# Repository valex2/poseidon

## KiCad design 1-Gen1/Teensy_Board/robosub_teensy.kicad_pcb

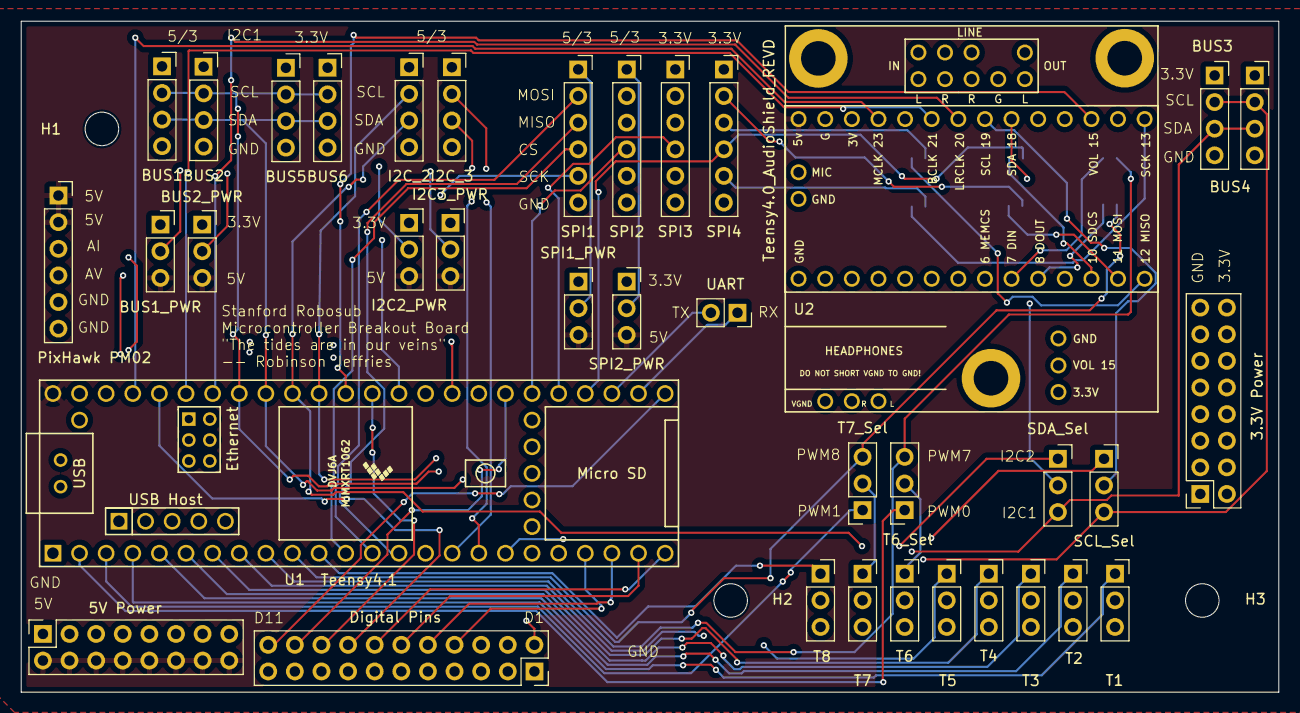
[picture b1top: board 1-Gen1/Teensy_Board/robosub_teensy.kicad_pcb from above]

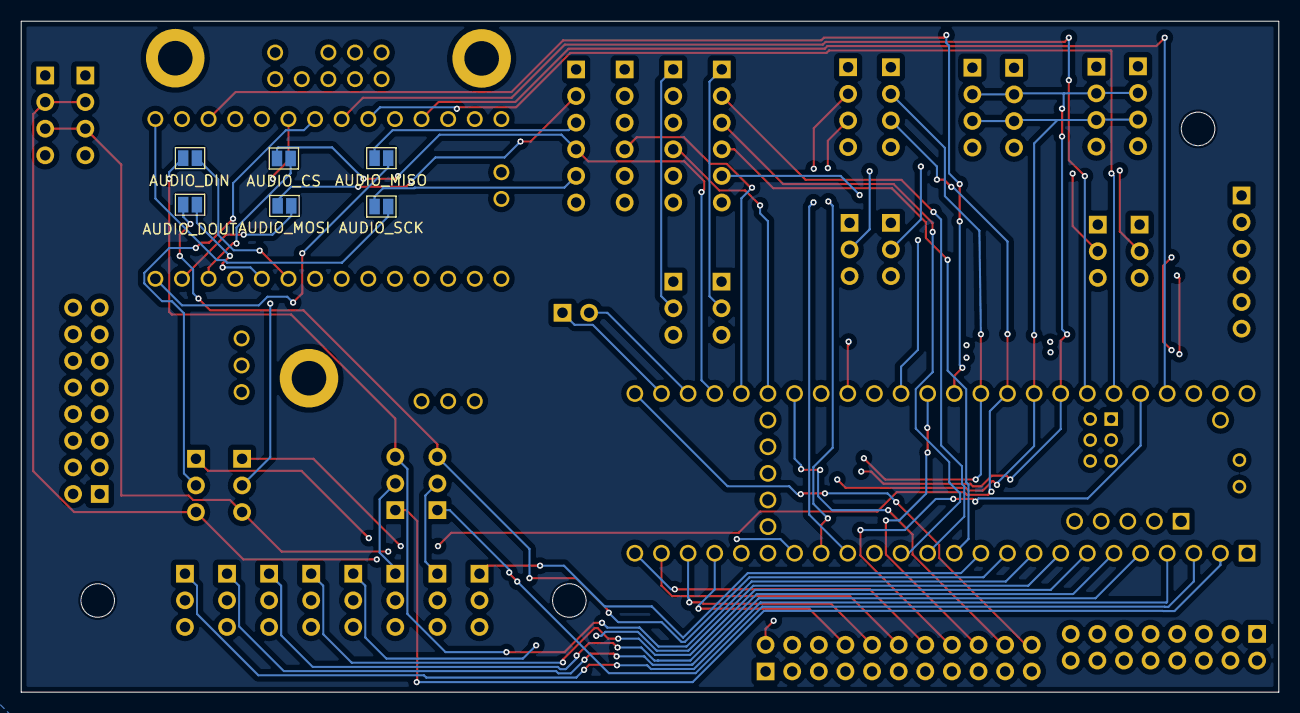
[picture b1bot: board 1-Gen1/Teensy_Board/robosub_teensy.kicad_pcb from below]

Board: 4 copper layers, 120.0 x 64.0 mm, 46 parts (6 on the bottom side), 61 nets.

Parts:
H1, H2, H3: MountingHole; MountingHole_3.2mm_M3
J1: T1; PinSocket_1x03_P2.54mm_Vertical
J2: UART; PinSocket_1x02_P2.54mm_Vertical
J3: T2; PinSocket_1x03_P2.54mm_Vertical
J4: T6; PinSocket_1x03_P2.54mm_Vertical
J5: T3; PinSocket_1x03_P2.54mm_Vertical
J6: T7; PinSocket_1x03_P2.54mm_Vertical
J7: T4; PinSocket_1x03_P2.54mm_Vertical
J8: T8; PinSocket_1x03_P2.54mm_Vertical
J9: T5; PinSocket_1x03_P2.54mm_Vertical
J10: PixHawk PM02; PinSocket_1x06_P2.54mm_Vertical
J11: 3.3V Power; PinSocket_2x08_P2.54mm_Vertical
J12: 5V Power; PinSocket_2x08_P2.54mm_Vertical
J13: BUS1; PinSocket_1x04_P2.54mm_Vertical
J14: BUS2; PinSocket_1x04_P2.54mm_Vertical
J17: Digital Pins; PinSocket_2x11_P2.54mm_Vertical
J18: BUS3; PinSocket_1x04_P2.54mm_Vertical
J19: BUS4; PinSocket_1x04_P2.54mm_Vertical
J20: BUS5; PinSocket_1x04_P2.54mm_Vertical
J21: BUS6; PinSocket_1x04_P2.54mm_Vertical
J22: SPI1; PinSocket_1x06_P2.54mm_Vertical
J23: SPI2; PinSocket_1x06_P2.54mm_Vertical
J24: I2C_2; PinSocket_1x04_P2.54mm_Vertical
J25: I2C_3; PinSocket_1x04_P2.54mm_Vertical
J26: SPI3; PinSocket_1x06_P2.54mm_Vertical
J27: SPI4; PinSocket_1x06_P2.54mm_Vertical
JP1: BUS1_PWR; PinSocket_1x03_P2.54mm_Vertical
JP2: BUS2_PWR; PinSocket_1x03_P2.54mm_Vertical
JP3: T6_Sel; PinSocket_1x03_P2.54mm_Vertical
JP4: T7_Sel; PinSocket_1x03_P2.54mm_Vertical
JP7: SPI1_PWR; PinSocket_1x03_P2.54mm_Vertical
JP8: SPI2_PWR; PinSocket_1x03_P2.54mm_Vertical
JP9: I2C2_PWR; PinSocket_1x03_P2.54mm_Vertical
JP10: I2C3_PWR; PinSocket_1x03_P2.54mm_Vertical
JP11: AUDIO_DIN; SolderJumper-2_P1.3mm_Open_Pad1.0x1.5mm
JP12: AUDIO_DOUT; SolderJumper-2_P1.3mm_Open_Pad1.0x1.5mm
JP13: AUDIO_CS; SolderJumper-2_P1.3mm_Open_Pad1.0x1.5mm
JP14: AUDIO_MOSI; SolderJumper-2_P1.3mm_Open_Pad1.0x1.5mm
JP15: AUDIO_MISO; SolderJumper-2_P1.3mm_Open_Pad1.0x1.5mm
JP16: AUDIO_SCK; SolderJumper-2_P1.3mm_Open_Pad1.0x1.5mm
JP17: SDA_Sel; PinSocket_1x03_P2.54mm_Vertical
JP18: SCL_Sel; PinSocket_1x03_P2.54mm_Vertical
U1: Teensy4.1; Teensy41
U2: Teensy4.0_AudioShield_REVD; 4.0audioshield

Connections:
+3.3V: J11.2, J11.4, J11.6, J11.8, J11.10, J11.12, J11.14, J11.16, J18.1, J19.1, J20.1, J21.1, J26.1, J27.1, JP1.1 (A), JP2.1 (A), JP7.1 (A), JP8.1 (A), JP9.1 (A), JP10.1 (A), U1.15 (3V3), U1.46 (3V3), U2.28 (3V)
+5V: J10.1, J10.2, J12.2, J12.4, J12.6, J12.8, J12.10, J12.12, J12.14, J12.16, JP1.3 (B), JP2.3 (B), JP7.3 (B), JP8.3 (B), JP9.3 (B), JP10.3 (B), U1.48 (VIN), U2.30 (5V)
Analog_Current: J10.3, U1.33 (41_A17)
Analog_Voltage: J10.4, U1.32 (40_A16)
BCLK: U1.43 (21_A7_RX5_BCLK1), U2.25 (21_A7_RX5_BCLK1)
D1/A1: J17.2, U1.18 (26_A12_MOSI1)
D2/A2: J17.4, U1.19 (27_A13_SCK1)
D3/PWM10: J17.6, U1.20 (28_RX7)
D4/PWM11: J17.8, U1.21 (29_TX7)
D5: J17.10, U1.22 (30_CRX3)
D6: J17.12, U1.23 (31_CTX3)
D7: J17.14, U1.24 (32_OUT1B)
D8/A3/PWM12: J17.16, U1.44 (22_A8_CTX1)
D9/A4/PWM13: J17.18, U1.36 (14_A0_TX3_SPDIF_OUT)
D10/A5: J17.20, U1.31 (39_MISO1_OUT1A)
D11/PWM14: J17.22, U1.25 (33_MCLK2)
GND: J1.3, J3.3, J4.3, J5.3, J6.3, J7.3, J8.3, J9.3, J10.5, J10.6, J11.1, J11.3, J11.5, J11.7, J11.9, J11.11, J11.13, J11.15, J12.1, J12.3, J12.5, J12.7, J12.9, J12.11, J12.13, J12.15, J13.4, J14.4, J17.1, J17.3, J17.5, J17.7, J17.9, J17.11, J17.13, J17.15, J17.17, J17.19, J17.21, J18.4, J19.4, J20.4, J21.4, J22.6, J23.6, J24.4, J25.4, J26.6, J27.6, U1.1 (GND), U1.34 (GND), U1.47 (GND), U2.1 (GND), U2.29 (GND)
I2C1_SCL: J13.2, J14.2, J18.2, J19.2, J20.2, J21.2, JP18.3 (B), U1.41 (19_A5_SCL)
I2C1_SDA: J13.3, J14.3, J18.3, J19.3, J20.3, J21.3, JP17.3 (B), U1.40 (18_A4_SDA)
I2C2_SCL: J24.2, JP18.1 (A), U1.38 (16_A2_RX4_SCL1)
I2C2_SDA: J24.3, JP17.1 (A), U1.39 (17_A3_TX4_SDA1)
I2C3_SCL: J25.2, U1.16 (24_A10_TX6_SCL2)
I2C3_SDA: J25.3, U1.17 (25_A11_RX6_SDA2)
LRCLK: U1.42 (20_A6_TX5_LRCLK1), U2.24 (20_A6_TX5_LRCLK1)
MCLK: U1.45 (23_A9_CRX1_MCLK1), U2.27 (23_A9_CRX1_MCLK1)
unnamed: J4.1, JP3.2 (C)
unnamed: J6.1, JP4.2 (C)
unnamed: J13.1, JP1.2 (C)
unnamed: J14.1, JP2.2 (C)
unnamed: J22.1, JP7.2 (C)
unnamed: J23.1, JP8.2 (C)
unnamed: J24.1, JP9.2 (C)
unnamed: J25.1, JP10.2 (C)
unnamed: JP11.2 (B), U2.9 (7_RX2_OUT1A)
unnamed: JP12.2 (B), U2.10 (8_TX2_IN1)
unnamed: JP13.2 (B), U2.12 (10_CS_MQSR)
unnamed: JP14.2 (B), U2.13 (11_MOSI_CTX1)
unnamed: JP15.2 (B), U2.14 (12_MISO_MQSL)
unnamed: JP16.2 (B), U2.17 (13_SCK_CRX1_LED)
unnamed: JP17.2 (C), U2.22 (18_A4_SDA0)
unnamed: JP18.2 (C), U2.23 (19_A5_SCL0)
PWM0: JP3.1 (A), U1.2 (0_RX1_CRX2_CS1)
PWM1: JP4.1 (A), U1.3 (1_TX1_CTX2_MISO1)
PWM2: J1.1, U1.4 (2_OUT2)
PWM3: J3.1, U1.5 (3_LRCLK2)
PWM4: J5.1, U1.6 (4_BCLK2)
PWM5: J7.1, U1.7 (5_IN2)
PWM6: J9.1, U1.8 (6_OUT1D)
PWM7/AUDIO_DIN: JP3.3 (B), JP11.1 (A), U1.9 (7_RX2_OUT1A)
PWM8/AUDIO_DOUT: JP4.3 (B), JP12.1 (A), U1.10 (8_TX2_IN1)
PWM9: J8.1, U1.11 (9_OUT1C)
SPI_CS1: J22.4, U1.12 (10_CS_MQSR)
SPI_CS2: J23.4, U1.30 (38_CS1_IN1)
SPI_CS3: J26.4, U1.29 (37_CS)
SPI_CS4: J27.4, JP13.1 (A), U1.28 (36_CS)
SPI_MISO: J22.3, J23.3, J26.3, J27.3, JP15.1 (A), U1.14 (12_MISO_MQSL)
SPI_MOSI: J22.2, J23.2, J26.2, J27.2, JP14.1 (A), U1.13 (11_MOSI_CTX1)
SPI_SCK: J22.5, J23.5, J26.5, J27.5, JP16.1 (A), U1.35 (13_SCK_LED)
UART_RX: J2.1, U1.26 (34_RX8)
UART_TX: J2.2, U1.27 (35_TX8)
Vol_Knob: U1.37 (15_A1_RX3_SPDIF_IN), U2.19 (15_A1_RX3_SPDIF_IN_VOL)

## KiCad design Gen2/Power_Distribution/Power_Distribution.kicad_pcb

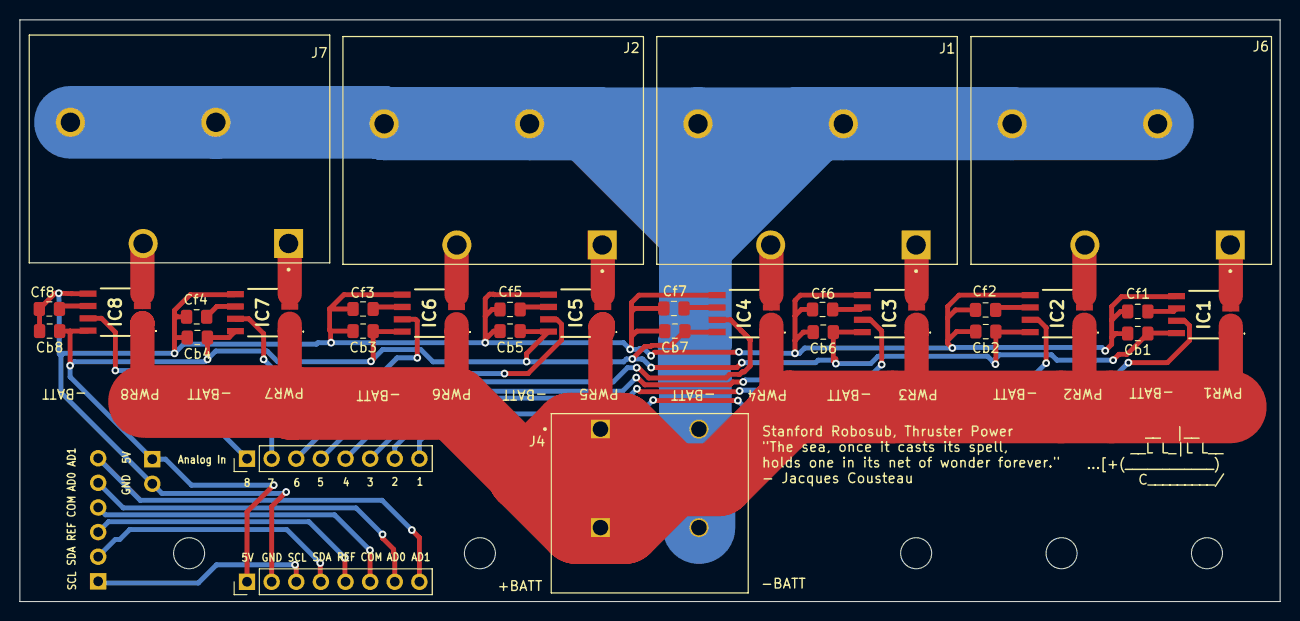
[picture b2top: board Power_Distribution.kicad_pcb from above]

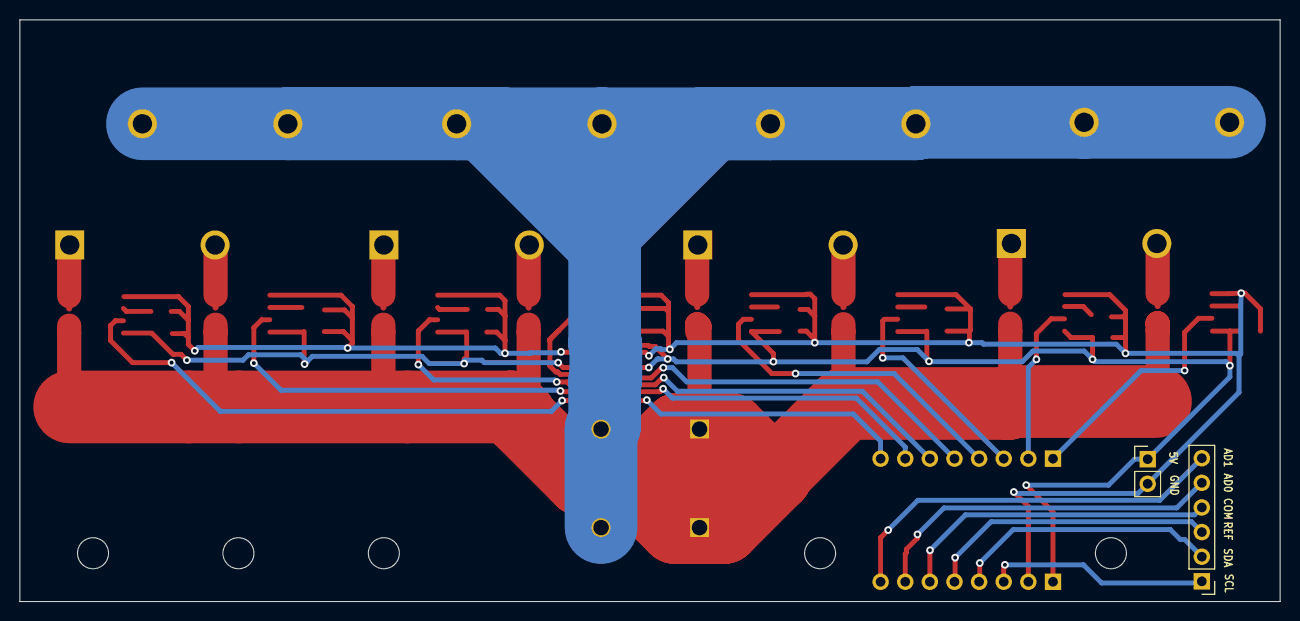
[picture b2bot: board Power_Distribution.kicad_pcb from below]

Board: 2 copper layers, 130.0 x 60.0 mm, 38 parts (2 on the bottom side), 34 nets.

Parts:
Cb1, Cb2, Cb3, Cb4, Cb5, Cb6, Cb7, Cb8: 0.1 µF; C_0805_2012Metric_Pad1.18x1.45mm_HandSolder
Cf1, Cf2, Cf3, Cf4, Cf5, Cf6, Cf7, Cf8: 100 µF; C_0805_2012Metric_Pad1.18x1.45mm_HandSolder
H1, H2, H2#2, H3, H4: MountingHole; MountingHole_3.2mm_M3
IC1, IC8: ACS713ELCTR-30A-T; ACS711ELCTR25ABT
IC2, IC3, IC4, IC5, IC6, IC7: ACS713ELCTR-30A-T; MyHalleffectSensor
J1, J2, J6, J7: 1098169; PHOENIX_1098169
J3, J9: Conn_01x08; PinHeader_1x08_P2.54mm_Vertical
J4: 1986660-2; TE_1986660-2
J5: Conn_01x06; PinHeader_1x06_P2.54mm_Vertical
J8: Conn_01x02; PinHeader_1x02_P2.54mm_Vertical

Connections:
5V: Cb1.1, Cb2.1, Cb3.1, Cb4.1, Cb5.1, Cb6.1, Cb7.1, Cb8.1, IC1.8 (VCC), IC2.8 (VCC), IC3.8 (VCC), IC4.8 (VCC), IC5.8 (VCC), IC6.8 (VCC), IC7.8 (VCC), IC8.8 (VCC), J3.1, J8.1
+BATT: IC1.1 (IP+_1), IC1.2 (IP+_2), IC2.1 (IP+_1), IC2.2 (IP+_2), IC3.1 (IP+_1), IC3.2 (IP+_2), IC4.1 (IP+_1), IC4.2 (IP+_2), IC5.1 (IP+_1), IC5.2 (IP+_2), IC6.1 (IP+_1), IC6.2 (IP+_2), IC7.1 (IP+_1), IC7.2 (IP+_2), IC8.1 (IP+_1), IC8.2 (IP+_2), J4.1_1 (1), J4.1_2 (1)
-BATT: J1.2, J1.4, J2.2, J2.4, J4.2_1 (2), J4.2_2 (2), J6.2, J6.4, J7.2, J7.4
AD0: J3.7, J5.5
AD1: J3.8, J5.6
COM: J3.6, J5.4
GND: Cb1.2, Cb2.2, Cb3.2, Cb4.2, Cb5.2, Cb6.2, Cb7.2, Cb8.2, Cf1.2, Cf2.2, Cf3.2, Cf4.2, Cf5.2, Cf6.2, Cf7.2, Cf8.2, IC1.5 (GND), IC2.5 (GND), IC3.5 (GND), IC4.5 (GND), IC5.5 (GND), IC6.5 (GND), IC7.5 (GND), IC8.5 (GND), J3.2, J8.2
unnamed: Cf1.1, IC1.6 (FILTER)
unnamed: Cf2.1, IC2.6 (FILTER)
unnamed: Cf6.1, IC3.6 (FILTER)
unnamed: Cf7.1, IC4.6 (FILTER)
unnamed: Cf5.1, IC5.6 (FILTER)
unnamed: Cf3.1, IC6.6 (FILTER)
unnamed: Cf4.1, IC7.6 (FILTER)
unnamed: Cf8.1, IC8.6 (FILTER)
PWR1: IC1.3 (IP-_1), IC1.4 (IP-_2), J6.1
PWR2: IC2.3 (IP-_1), IC2.4 (IP-_2), J6.3
PWR3: IC3.3 (IP-_1), IC3.4 (IP-_2), J1.1
PWR4: IC4.3 (IP-_1), IC4.4 (IP-_2), J1.3
PWR5: IC5.3 (IP-_1), IC5.4 (IP-_2), J2.1
PWR6: IC6.3 (IP-_1), IC6.4 (IP-_2), J2.3
PWR7: IC7.3 (IP-_1), IC7.4 (IP-_2), J7.1
PWR8: IC8.3 (IP-_1), IC8.4 (IP-_2), J7.3
REF: J3.5, J5.3
SCL: J3.3, J5.1
SDA: J3.4, J5.2
VIout1: IC1.7 (VIOUT), J9.8
VIout2: IC2.7 (VIOUT), J9.7
VIout3: IC3.7 (VIOUT), J9.6
VIout4: IC4.7 (VIOUT), J9.5
VIout5: IC5.7 (VIOUT), J9.4
VIout6: IC6.7 (VIOUT), J9.3
VIout7: IC7.7 (VIOUT), J9.2
VIout8: IC8.7 (VIOUT), J9.1

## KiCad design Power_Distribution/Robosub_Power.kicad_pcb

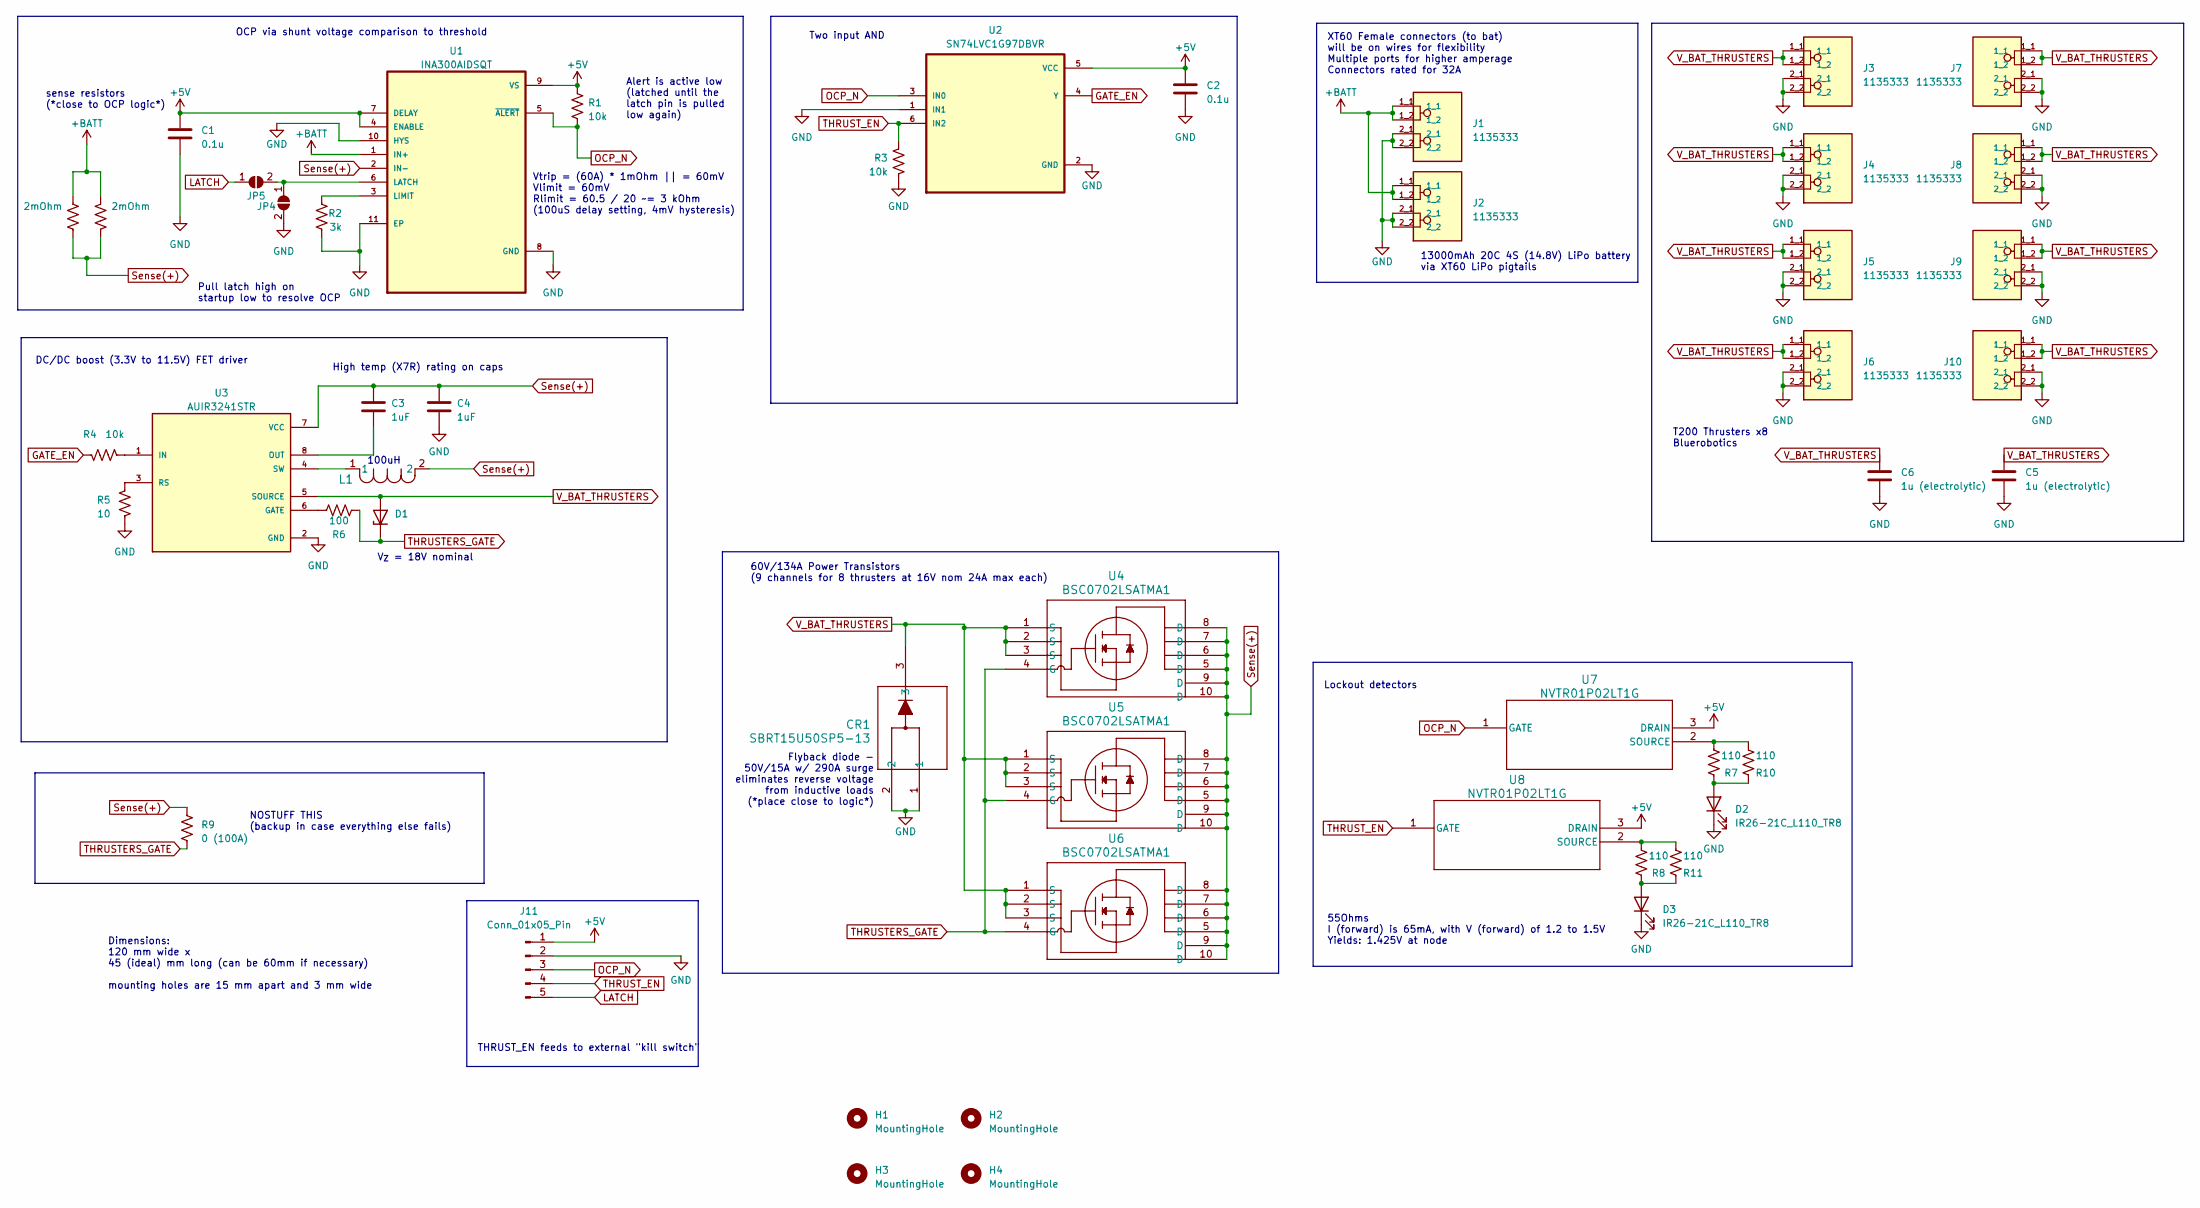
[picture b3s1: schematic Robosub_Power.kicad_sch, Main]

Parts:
C1, C2: 0.1u; C_0805_2012Metric_Pad1.18x1.45mm_HandSolder
C3, C4: 1uF; C_1812_4532Metric_Pad1.57x3.40mm_HandSolder
C5, C6: 1u (electrolytic); UCB1V0R1MCL1GS
CR1: SBRT15U50SP5-13; POWERDI5_DIO
D1: 1SMA5931BT3; D_SMA
D2, D3: IR26-21C_L110_TR8; LED_1206_3216Metric
H1, H2, H3, H4: MountingHole; MountingHole_3.2mm_M3
J1, J2, J3, J4, J5, J6, J7, J8, J9, J10: 1135333; PHOENIX_1135333
J11: Conn_01x05_Pin; PinHeader_1x05_P2.54mm_Vertical
JP4, JP5: SolderJumper_2_Open; SolderJumper-2_P1.3mm_Open_Pad1.0x1.5mm
L1: 74477420; IND_5848-WE-PD2_WRE
R1, R3, R4: 10k; R_0805_2012Metric_Pad1.20x1.40mm_HandSolder
R2: 3k; R_0805_2012Metric_Pad1.20x1.40mm_HandSolder
R5: 10; R_0805_2012Metric_Pad1.20x1.40mm_HandSolder
R6: 100; R_0805_2012Metric_Pad1.20x1.40mm_HandSolder
R7, R8, R10, R11: 110; R_0805_2012Metric_Pad1.20x1.40mm_HandSolder
R9: 0 (100A); R_2512_6332Metric_Pad1.40x3.35mm_HandSolder
U1: INA300AIDSQT; SON40P200X200X80-11N
U2: SN74LVC1G97DBVR; SOT95P280X145-6N
U3: AUIR3241STR; SOIC127P600X175-8N_AUIR3241STR
U4, U5, U6: BSC0702LSATMA1
U7, U8: NVTR01P02LT1G; SOT-23-3_1P4X3P040_ONS
WSLP59312L000FEA_1, WSLP59312L000FEA_2: 2mOhm; RES_WSLP5931_.002OHM_VIS

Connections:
+5V: C1.1, C2.1, J11.1, R1.1, U1.4 (ENABLE), U1.7 (DELAY), U1.9 (VS), U2.5 (VCC), U7.3 (DRAIN), U8.3 (DRAIN)
+BATT: J1.1_1, J1.1_2, J2.1_1, J2.1_2, U1.1 (IN+), WSLP59312L000FEA_1.2, WSLP59312L000FEA_2.2
GATE_EN: R4.1, U2.4 (Y)
GND: C1.2, C2.2, C4.2, C5.2, C6.2, CR1.1, CR1.2, D2.1 (K), D3.1 (K), J1.2_1, J1.2_2, J2.2_1, J2.2_2, J3.2_1, J3.2_2, J4.2_1, J4.2_2, J5.2_1, J5.2_2, J6.2_1, J6.2_2, J7.2_1, J7.2_2, J8.2_1, J8.2_2, J9.2_1, J9.2_2, J10.2_1, J10.2_2, J11.2, JP4.2 (B), R2.2, R3.2, R5.2, U1.8 (GND), U1.10 (HYS), U1.11 (EP), U2.1 (IN1), U2.2 (GND), U3.2 (GND)
LATCH: J11.5, JP5.1 (A)
unnamed: D2.2 (A), R7.1, R10.1
unnamed: D3.2 (A), R8.1, R11.1
unnamed: JP4.1 (A), JP5.2 (B), U1.6 (LATCH)
unnamed: R2.1, U1.3 (LIMIT)
unnamed: R6.1, U3.6 (GATE)
unnamed: R4.2, U3.1 (IN)
unnamed: C3.2, U3.8 (OUT)
unnamed: R5.1, U3.3 (RS)
unnamed: L1.1, U3.4 (SW)
unnamed: R7.2, R10.2, U7.2 (SOURCE)
unnamed: R8.2, R11.2, U8.2 (SOURCE)
OCP_N: J11.3, R1.2, U1.5 (~ALERT), U2.3 (IN0), U7.1 (GATE)
Sense(+): C3.1, C4.1, L1.2, R9.1, U1.2 (IN-), U3.7 (VCC), U4.5 (D), U4.6 (D), U4.7 (D), U4.8 (D), U4.9 (D), U4.10 (D), U5.5 (D), U5.6 (D), U5.7 (D), U5.8 (D), U5.9 (D), U5.10 (D), U6.5 (D), U6.6 (D), U6.7 (D), U6.8 (D), U6.9 (D), U6.10 (D), WSLP59312L000FEA_1.1, WSLP59312L000FEA_2.1
THRUSTERS_GATE: D1.1 (K), R6.2, R9.2, U4.4 (G), U5.4 (G), U6.4 (G)
THRUST_EN: J11.4, R3.1, U2.6 (IN2), U8.1 (GATE)
V_BAT_THRUSTERS: C5.1, C6.1, CR1.3, D1.2 (A), J3.1_1, J3.1_2, J4.1_1, J4.1_2, J5.1_1, J5.1_2, J6.1_1, J6.1_2, J7.1_1, J7.1_2, J8.1_1, J8.1_2, J9.1_1, J9.1_2, J10.1_1, J10.1_2, U3.5 (SOURCE), U4.1 (S), U4.2 (S), U4.3 (S), U5.1 (S), U5.2 (S), U5.3 (S), U6.1 (S), U6.2 (S), U6.3 (S)

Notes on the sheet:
THRUST_EN feeds to external "kill switch"
Two input AND
Lockout detectors
Dimensions: 120 mm wide x 45 (ideal) mm long (can be 60mm if necessary) mounting holes are 15 mm apart and 3 mm wide
High temp (X7R) rating on caps
13000mAh 20C 4S (14.8V) LiPo battery via XT60 LiPo pigtails
Vtrip = (60A) * 1mOhm || = 60mV Vlimit = 60mV Rlimit = 60.5 / 20 ~= 3 kOhm (100uS delay setting, 4mV hysteresis)
Alert is active low (latched until the latch pin is pulled low again)
DC/DC boost (3.3V to 11.5V) FET driver
55Ohms I (forward) is 65mA, with V (forward) of 1.2 to 1.5V Yields: 1.425V at node
XT60 Female connectors (to bat) will be on wires for flexibility Multiple ports for higher amperage Connectors rated for 32A
Flyback diode - 50V/15A w/ 290A surge eliminates reverse voltage from inductive loads (*place close to logic*)
60V/134A Power Transistors (9 channels for 8 thrusters at 16V nom 24A max each)
V_{Z} = 18V nominal
100uH
NOSTUFF THIS (backup in case everything else fails)
T200 Thrusters x8 Bluerobotics
OCP via shunt voltage comparison to threshold
Pull latch high on startup low to resolve OCP
sense resistors (*close to OCP logic*)

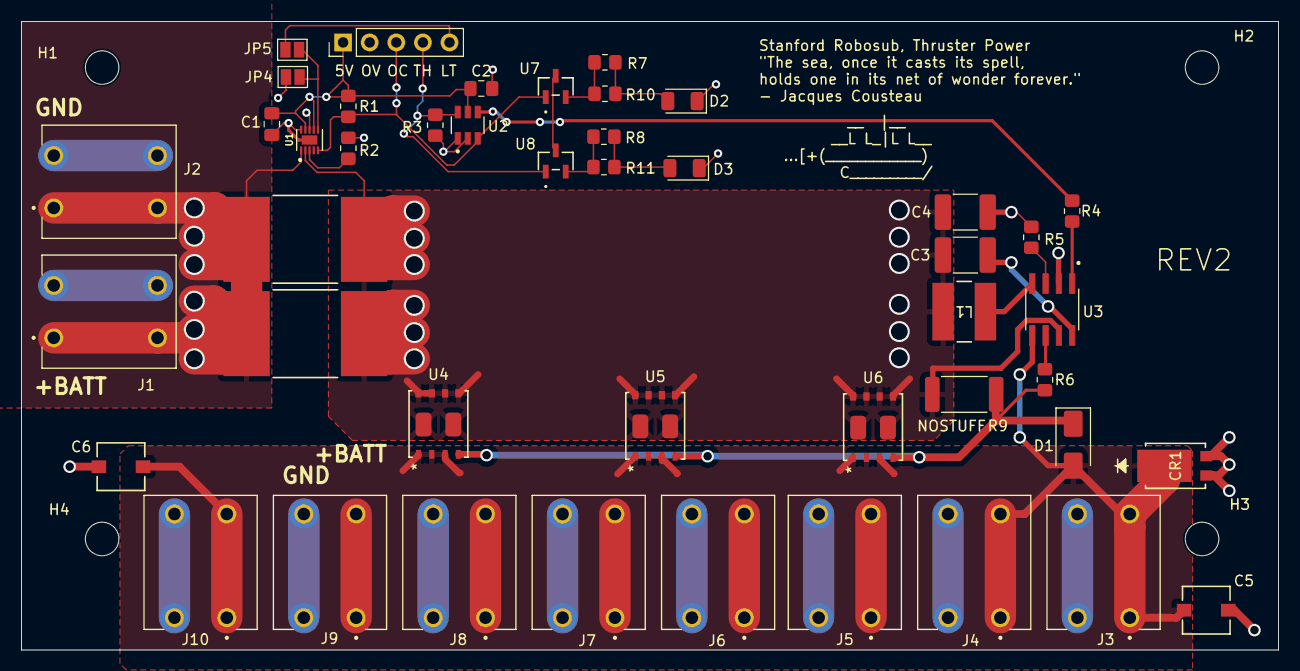
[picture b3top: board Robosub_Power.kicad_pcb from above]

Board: 2 copper layers, 120.0 x 60.0 mm, 49 parts (0 on the bottom side), 21 nets.

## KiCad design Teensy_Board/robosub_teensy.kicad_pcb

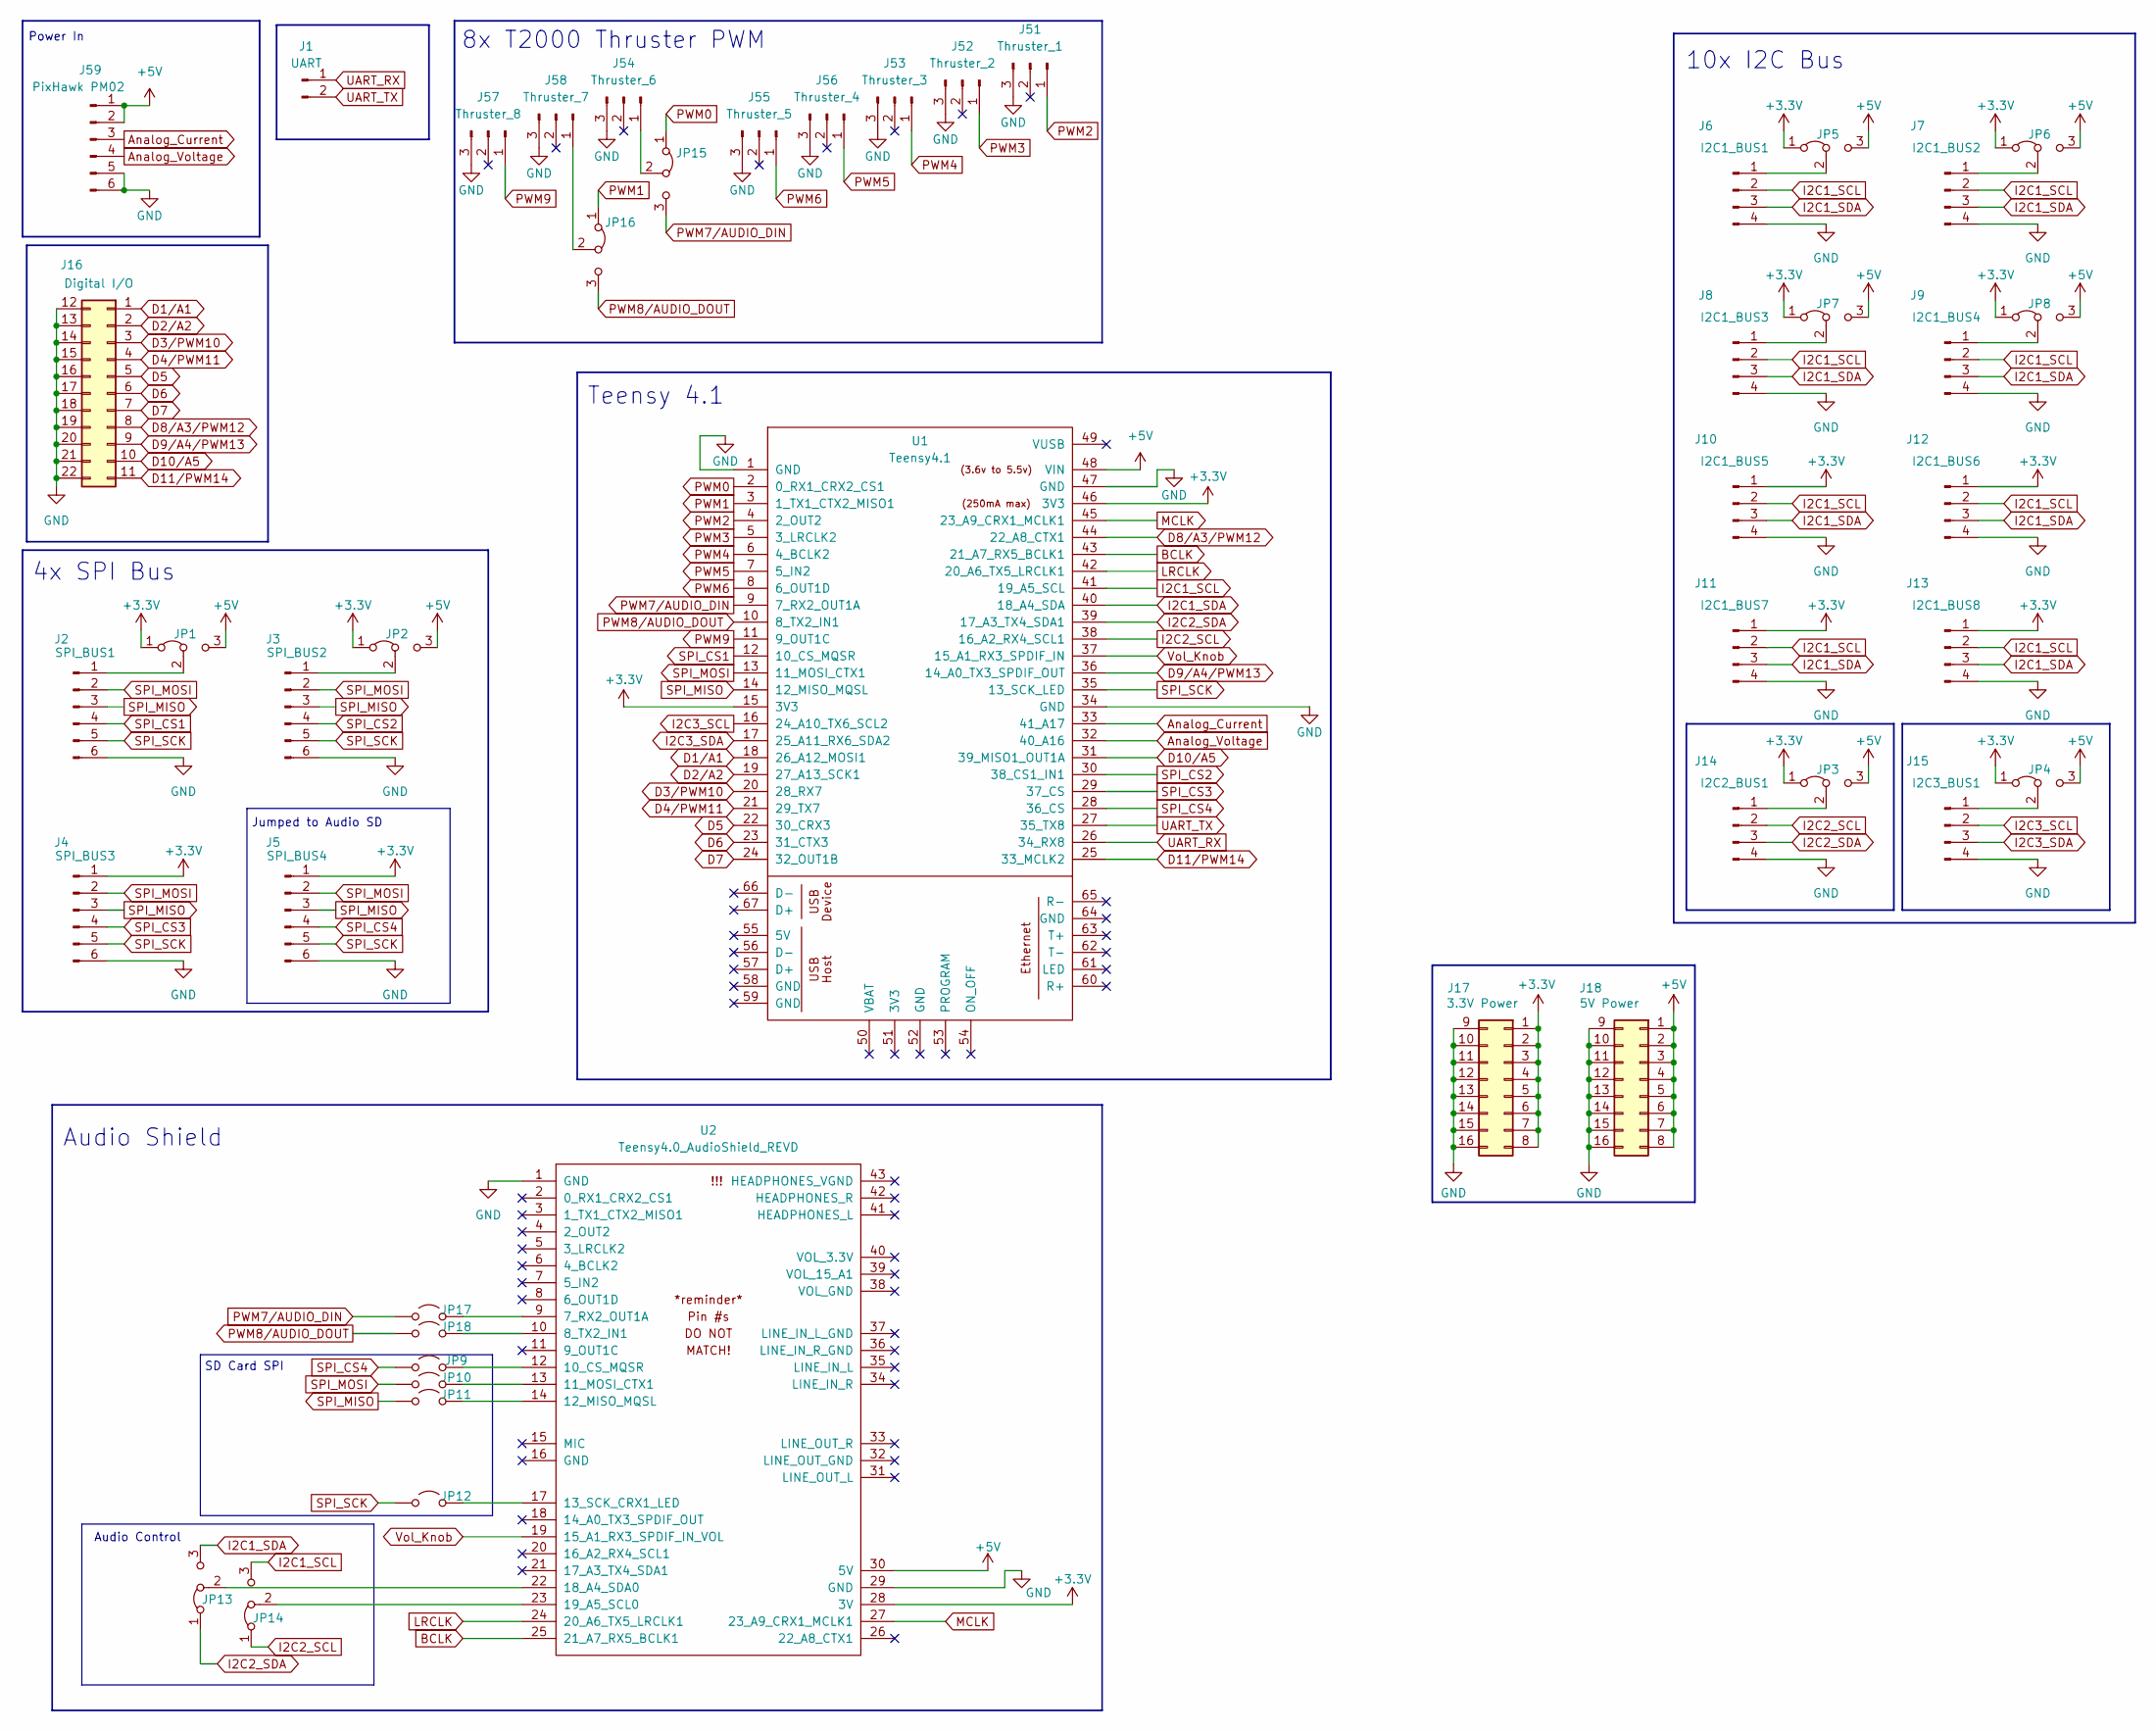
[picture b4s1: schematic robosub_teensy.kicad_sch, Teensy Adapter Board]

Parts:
J1: UART; PinSocket_1x02_P2.54mm_Vertical
J2: SPI_BUS1; PinSocket_1x06_P2.54mm_Vertical
J3: SPI_BUS2; PinSocket_1x06_P2.54mm_Vertical
J4: SPI_BUS3; PinSocket_1x06_P2.54mm_Vertical
J5: SPI_BUS4; PinSocket_1x06_P2.54mm_Vertical
J6: I2C1_BUS1; PinSocket_1x04_P2.54mm_Vertical
J7: I2C1_BUS2; PinSocket_1x04_P2.54mm_Vertical
J8: I2C1_BUS3; PinSocket_1x04_P2.54mm_Vertical
J9: I2C1_BUS4; PinSocket_1x04_P2.54mm_Vertical
J10: I2C1_BUS5; PinSocket_1x04_P2.54mm_Vertical
J11: I2C1_BUS7; PinSocket_1x04_P2.54mm_Vertical
J12: I2C1_BUS6; PinSocket_1x04_P2.54mm_Vertical
J13: I2C1_BUS8; PinSocket_1x04_P2.54mm_Vertical
J14: I2C2_BUS1; PinSocket_1x04_P2.54mm_Vertical
J15: I2C3_BUS1; PinSocket_1x04_P2.54mm_Vertical
J16: Digital I/O
J17: 3.3V Power; PinSocket_2x08_P2.54mm_Vertical
J18: 5V Power; PinSocket_2x08_P2.54mm_Vertical
J51: Thruster_1; PinSocket_1x03_P2.54mm_Vertical
J52: Thruster_2; PinSocket_1x03_P2.54mm_Vertical
J53: Thruster_3; PinSocket_1x03_P2.54mm_Vertical
J54: Thruster_6; PinSocket_1x03_P2.54mm_Vertical
J55: Thruster_5; PinSocket_1x03_P2.54mm_Vertical
J56: Thruster_4; PinSocket_1x03_P2.54mm_Vertical
J57: Thruster_8; PinSocket_1x03_P2.54mm_Vertical
J58: Thruster_7; PinSocket_1x03_P2.54mm_Vertical
J59: PixHawk PM02; PinSocket_1x06_P2.54mm_Vertical
JP1, JP2, JP3, JP4, JP5, JP6, JP7, JP8, JP13, JP14, JP15, JP16: Jumper_3_Bridged12; PinSocket_1x03_P2.54mm_Vertical
JP9, JP10, JP11, JP12, JP17, JP18: Jumper_2_Open; PinSocket_1x02_P2.54mm_Vertical
U1: Teensy4.1; Teensy41
U2: Teensy4.0_AudioShield_REVD; 4.0audioshield

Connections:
+3.3V: J4.1, J5.1, J10.1, J11.1, J12.1, J13.1, J17.1, J17.2, J17.3, J17.4, J17.5, J17.6, J17.7, J17.8, JP1.1 (A), JP2.1 (A), JP3.1 (A), JP4.1 (A), JP5.1 (A), JP6.1 (A), JP7.1 (A), JP8.1 (A), U1.15 (3V3), U1.46 (3V3), U2.28 (3V)
+5V: J18.1, J18.2, J18.3, J18.4, J18.5, J18.6, J18.7, J18.8, J59.1, J59.2, JP1.3 (B), JP2.3 (B), JP3.3 (B), JP4.3 (B), JP5.3 (B), JP6.3 (B), JP7.3 (B), JP8.3 (B), U1.48 (VIN), U2.30 (5V)
Analog_Current: J59.3, U1.33 (41_A17)
Analog_Voltage: J59.4, U1.32 (40_A16)
BCLK: U1.43 (21_A7_RX5_BCLK1), U2.25 (21_A7_RX5_BCLK1)
D1/A1: J16.1, U1.18 (26_A12_MOSI1)
D2/A2: J16.2, U1.19 (27_A13_SCK1)
D3/PWM10: J16.3, U1.20 (28_RX7)
D4/PWM11: J16.4, U1.21 (29_TX7)
D5: J16.5, U1.22 (30_CRX3)
D6: J16.6, U1.23 (31_CTX3)
D7: J16.7, U1.24 (32_OUT1B)
D8/A3/PWM12: J16.8, U1.44 (22_A8_CTX1)
D9/A4/PWM13: J16.9, U1.36 (14_A0_TX3_SPDIF_OUT)
D10/A5: J16.10, U1.31 (39_MISO1_OUT1A)
D11/PWM14: J16.11, U1.25 (33_MCLK2)
GND: J2.6, J3.6, J4.6, J5.6, J6.4, J7.4, J8.4, J9.4, J10.4, J11.4, J12.4, J13.4, J14.4, J15.4, J16.12, J16.13, J16.14, J16.15, J16.16, J16.17, J16.18, J16.19, J16.20, J16.21, J16.22, J17.9, J17.10, J17.11, J17.12, J17.13, J17.14, J17.15, J17.16, J18.9, J18.10, J18.11, J18.12, J18.13, J18.14, J18.15, J18.16, J51.3, J52.3, J53.3, J54.3, J55.3, J56.3, J57.3, J58.3, J59.5, J59.6, U1.1 (GND), U1.34 (GND), U1.47 (GND), U2.1 (GND), U2.29 (GND)
I2C1_SCL: J6.2, J7.2, J8.2, J9.2, J10.2, J11.2, J12.2, J13.2, JP14.3 (B), U1.41 (19_A5_SCL)
I2C1_SDA: J6.3, J7.3, J8.3, J9.3, J10.3, J11.3, J12.3, J13.3, JP13.3 (B), U1.40 (18_A4_SDA)
I2C2_SCL: J14.2, JP14.1 (A), U1.38 (16_A2_RX4_SCL1)
I2C2_SDA: J14.3, JP13.1 (A), U1.39 (17_A3_TX4_SDA1)
I2C3_SCL: J15.2, U1.16 (24_A10_TX6_SCL2)
I2C3_SDA: J15.3, U1.17 (25_A11_RX6_SDA2)
LRCLK: U1.42 (20_A6_TX5_LRCLK1), U2.24 (20_A6_TX5_LRCLK1)
MCLK: U1.45 (23_A9_CRX1_MCLK1), U2.27 (23_A9_CRX1_MCLK1)
unnamed: J2.1, JP1.2 (C)
unnamed: J3.1, JP2.2 (C)
unnamed: J6.1, JP5.2 (C)
unnamed: J7.1, JP6.2 (C)
unnamed: J8.1, JP7.2 (C)
unnamed: J9.1, JP8.2 (C)
unnamed: J14.1, JP3.2 (C)
unnamed: J15.1, JP4.2 (C)
unnamed: J54.1, JP15.2 (C)
unnamed: J58.1, JP16.2 (C)
unnamed: JP9.2 (B), U2.12 (10_CS_MQSR)
unnamed: JP10.2 (B), U2.13 (11_MOSI_CTX1)
unnamed: JP11.2 (B), U2.14 (12_MISO_MQSL)
unnamed: JP12.2 (B), U2.17 (13_SCK_CRX1_LED)
unnamed: JP13.2 (C), U2.22 (18_A4_SDA0)
unnamed: JP14.2 (C), U2.23 (19_A5_SCL0)
unnamed: JP17.2 (B), U2.9 (7_RX2_OUT1A)
unnamed: JP18.2 (B), U2.10 (8_TX2_IN1)
PWM0: JP15.1 (A), U1.2 (0_RX1_CRX2_CS1)
PWM1: JP16.1 (A), U1.3 (1_TX1_CTX2_MISO1)
PWM2: J51.1, U1.4 (2_OUT2)
PWM3: J52.1, U1.5 (3_LRCLK2)
PWM4: J53.1, U1.6 (4_BCLK2)
PWM5: J56.1, U1.7 (5_IN2)
PWM6: J55.1, U1.8 (6_OUT1D)
PWM7/AUDIO_DIN: JP15.3 (B), JP17.1 (A), U1.9 (7_RX2_OUT1A)
PWM8/AUDIO_DOUT: JP16.3 (B), JP18.1 (A), U1.10 (8_TX2_IN1)
PWM9: J57.1, U1.11 (9_OUT1C)
SPI_CS1: J2.4, U1.12 (10_CS_MQSR)
SPI_CS2: J3.4, U1.30 (38_CS1_IN1)
SPI_CS3: J4.4, U1.29 (37_CS)
SPI_CS4: J5.4, JP9.1 (A), U1.28 (36_CS)
SPI_MISO: J2.3, J3.3, J4.3, J5.3, JP11.1 (A), U1.14 (12_MISO_MQSL)
SPI_MOSI: J2.2, J3.2, J4.2, J5.2, JP10.1 (A), U1.13 (11_MOSI_CTX1)
SPI_SCK: J2.5, J3.5, J4.5, J5.5, JP12.1 (A), U1.35 (13_SCK_LED)
UART_RX: J1.1, U1.26 (34_RX8)
UART_TX: J1.2, U1.27 (35_TX8)
Vol_Knob: U1.37 (15_A1_RX3_SPDIF_IN), U2.19 (15_A1_RX3_SPDIF_IN_VOL)

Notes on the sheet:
8x T2000 Thruster PWM
4x SPI Bus
Teensy 4.1
Audio Control
SD Card SPI
Power In
Audio Shield
Jumped to Audio SD
10x I2C Bus

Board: 2 copper layers, 46 parts (0 on the bottom side), 52 nets, no tracks yet.
